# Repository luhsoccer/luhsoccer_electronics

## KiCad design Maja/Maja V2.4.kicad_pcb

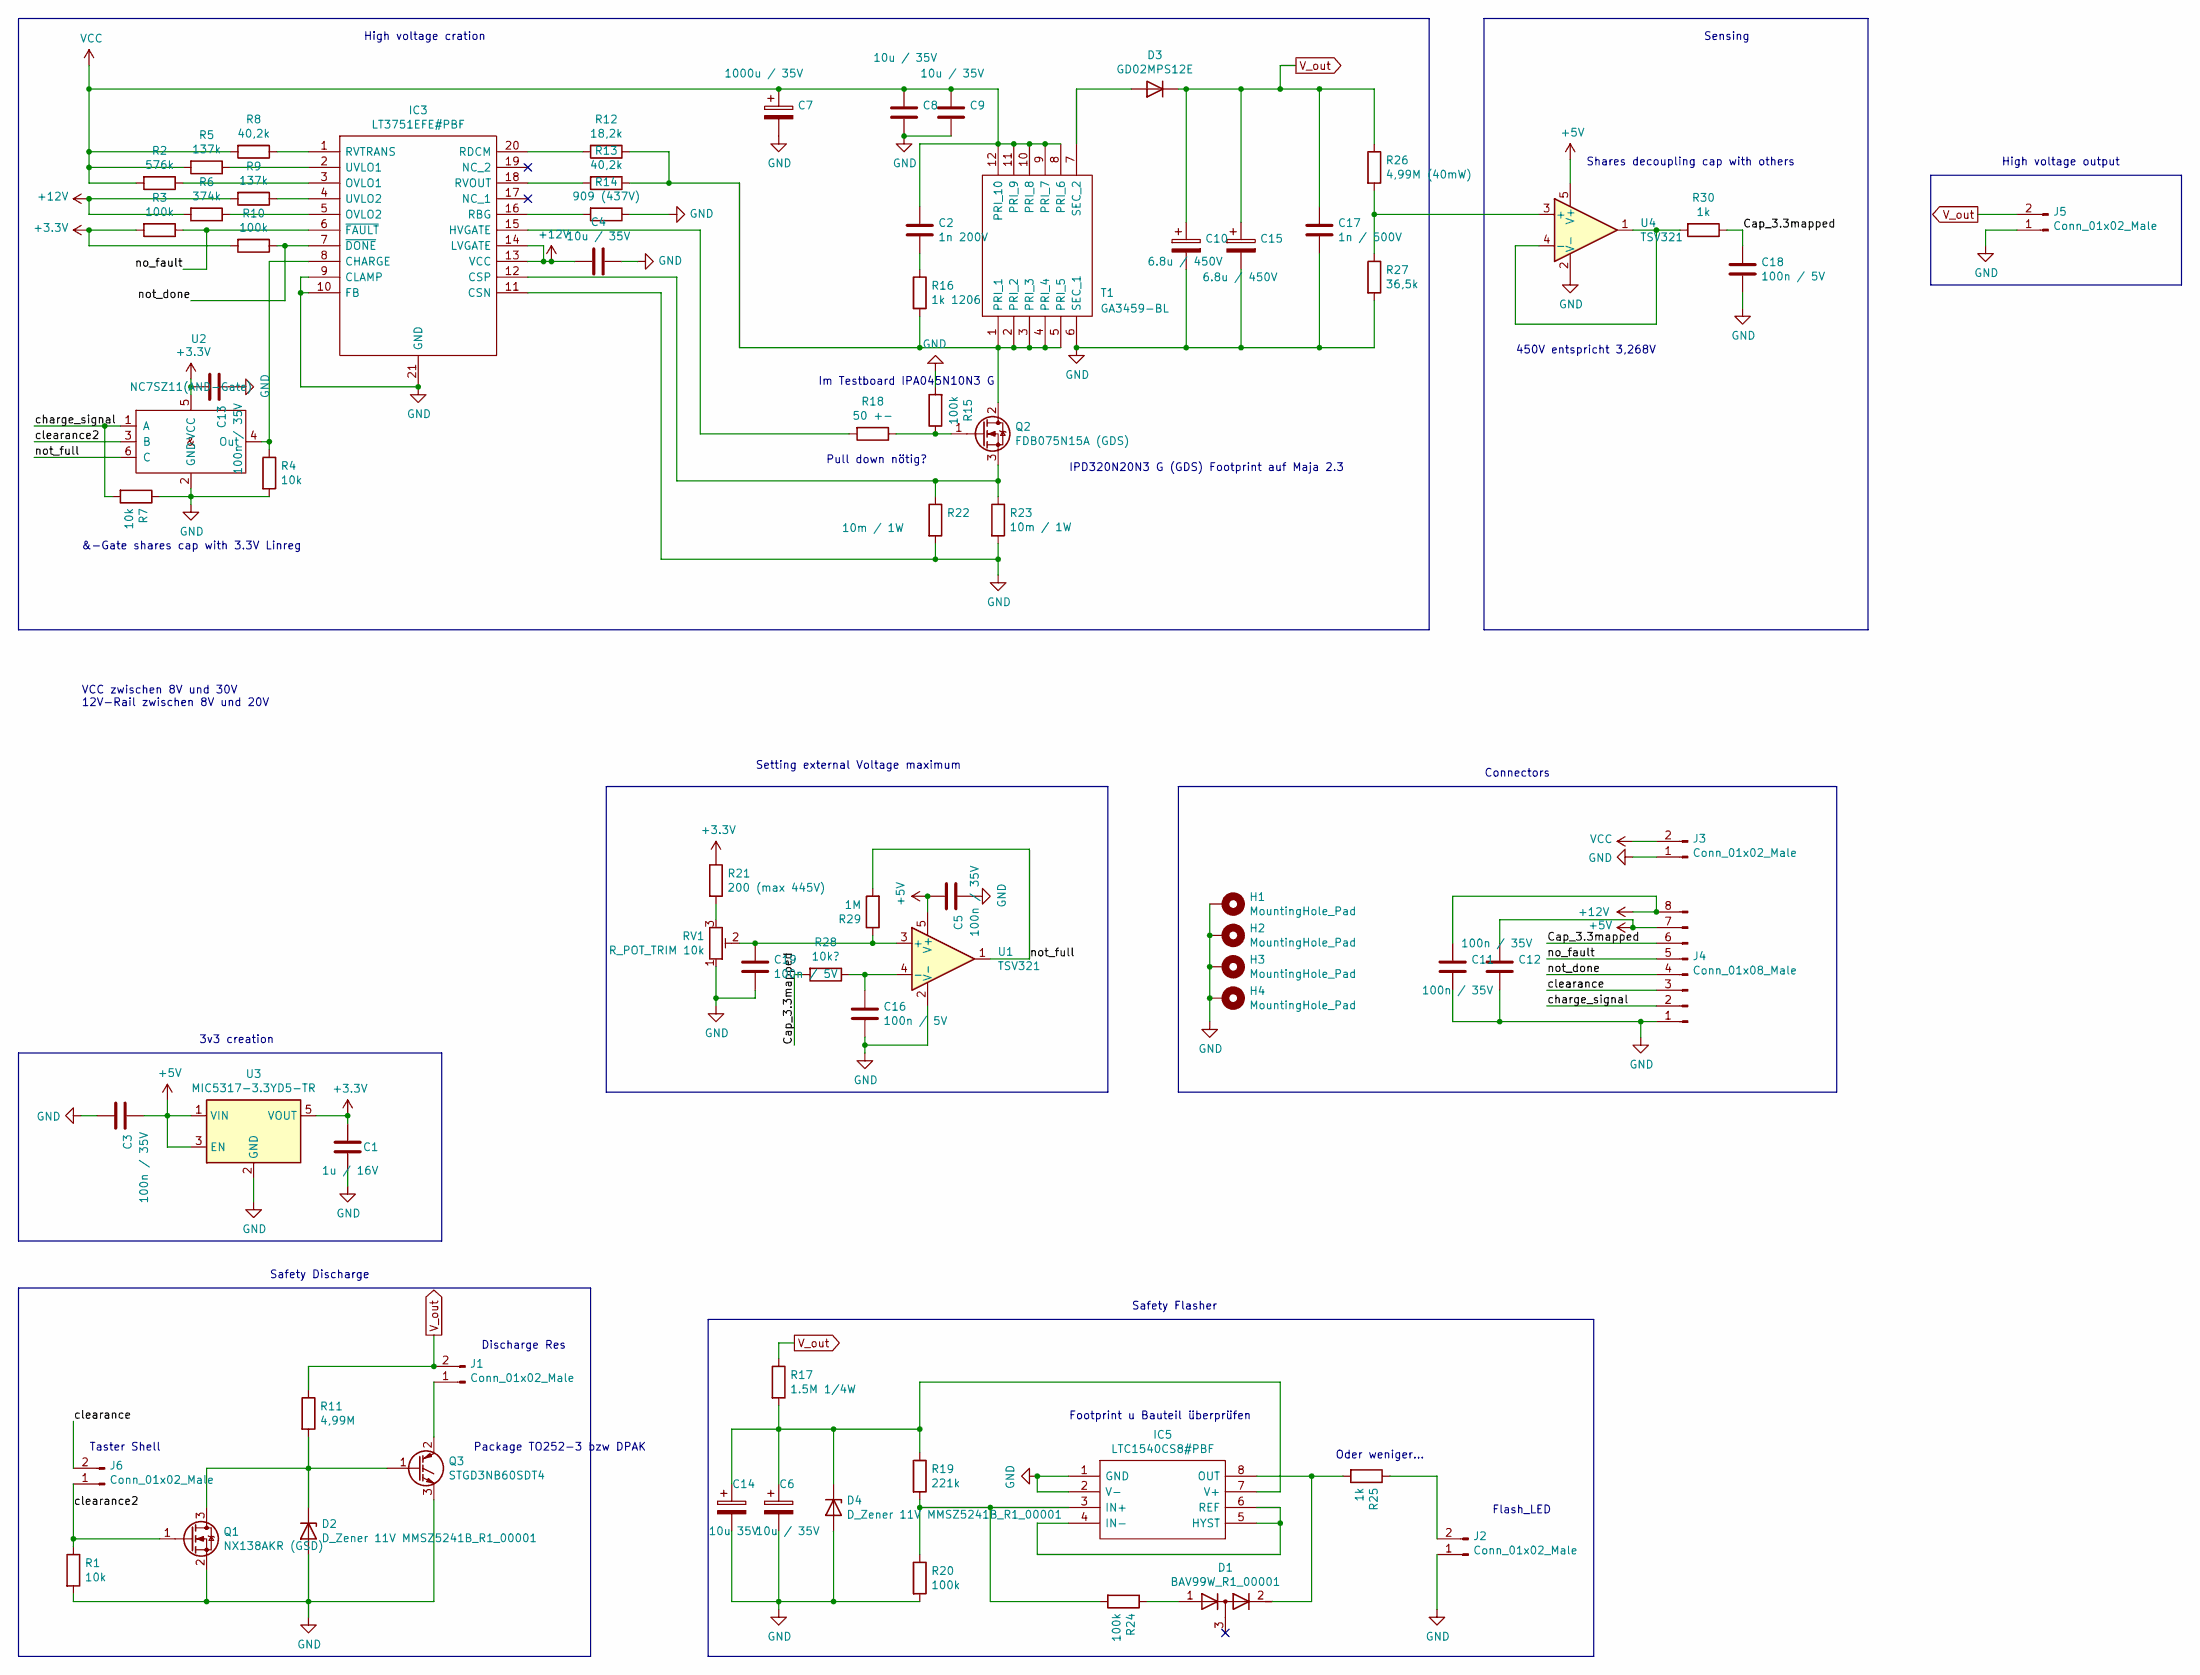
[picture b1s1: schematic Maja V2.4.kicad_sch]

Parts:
C1: 1u / 16V; C_0805_2012Metric_Pad1.15x1.40mm_HandSolder
C2: 1n 200V; C_1206_3216Metric_Pad1.42x1.75mm_HandSolder
C3, C5, C11, C12, C13: 100n / 35V; C_0805_2012Metric_Pad1.15x1.40mm_HandSolder
C4, C6, C8, C9: 10u / 35V; C_0805_2012Metric_Pad1.15x1.40mm_HandSolder
C7: 1000u / 35V; CP_Radial_D16.0mm_P7.50mm
C10, C15: 6.8u / 450V; CP_Radial_D10.0mm_P5.00mm
C14: 10u 35V; C_0805_2012Metric_Pad1.15x1.40mm_HandSolder
C16, C18, C19: 100n / 5V; C_0805_2012Metric_Pad1.15x1.40mm_HandSolder
C17: 1n / 500V; C_1206_3216Metric_Pad1.42x1.75mm_HandSolder
D1: BAV99W_R1_00001; SOT-323_SC-70_Handsoldering
D2, D4: D_Zener 11V MMSZ5241B_R1_00001; D_SOD-123
D3: GD02MPS12E; TO-252-2_TabPin1
H1, H2, H3, H4: MountingHole_Pad; MountingHole_3.2mm_M3_Pad_Via
IC3: LT3751EFE#PBF; SOP65P640X120-21N; Mouser Part Number 584-LT3751EFE#PBF
IC5: LTC1540CS8#PBF; SO-8_3.9x4.9mm_P1.27mm; Mouser Part Number 584-LTC1540IMS8#PBF
J1, J3, J5: Conn_01x02_Male; Molex_Micro-Fit_3.0_43650-0200_1x02_P3.00mm_Horizontal
J2, J6: Conn_01x02_Male; JST_PH_S2B-PH-K_1x02_P2.00mm_Horizontal
J4: Conn_01x08_Male; JST_PH_S8B-PH-K_1x08_P2.00mm_Horizontal
Q1: NX138AKR (GSD); SOT-23_Handsoldering
Q2: FDB075N15A (GDS); TO-263-2
Q3: STGD3NB60SDT4; TO-252-2
R1, R4, R7: 10k; R_0805_2012Metric_Pad1.15x1.40mm_HandSolder
R2: 576k; R_0805_2012Metric_Pad1.15x1.40mm_HandSolder
R3, R10, R15, R20, R24: 100k; R_0805_2012Metric_Pad1.15x1.40mm_HandSolder
R5, R9: 137k; R_0805_2012Metric_Pad1.15x1.40mm_HandSolder
R6: 374k; R_0805_2012Metric_Pad1.15x1.40mm_HandSolder
R8, R13: 40,2k; R_0805_2012Metric_Pad1.15x1.40mm_HandSolder
R11: 4,99M; R_2010_5025Metric_Pad1.52x2.65mm_HandSolder
R12: 18,2k; R_0805_2012Metric_Pad1.15x1.40mm_HandSolder
R14: 909 (437V); R_0805_2012Metric_Pad1.15x1.40mm_HandSolder
R16: 1k 1206; R_1206_3216Metric_Pad1.42x1.75mm_HandSolder
R17: 1.5M 1/4W; R_2010_5025Metric_Pad1.52x2.65mm_HandSolder
R18: 50 +-; R_0805_2012Metric_Pad1.15x1.40mm_HandSolder
R19: 221k; R_0805_2012Metric_Pad1.15x1.40mm_HandSolder
R21: 200 (max 445V); R_0805_2012Metric_Pad1.15x1.40mm_HandSolder
R22, R23: 10m / 1W; R_1206_3216Metric_Pad1.42x1.75mm_HandSolder
R25, R30: 1k; R_0805_2012Metric_Pad1.15x1.40mm_HandSolder
R26: 4,99M (40mW); R_2010_5025Metric_Pad1.52x2.65mm_HandSolder
R27: 36,5k; R_0805_2012Metric_Pad1.15x1.40mm_HandSolder
R28: 10k?; R_0805_2012Metric_Pad1.15x1.40mm_HandSolder
R29: 1M; R_0805_2012Metric_Pad1.15x1.40mm_HandSolder
RV1: R_POT_TRIM 10k; Potentiometer_Bourns_3266Z_Horizontal
T1: GA3459-BL; GA3459BL; Mouser Part Number 994-GA3459-BL
U1, U4: TSV321; TSOT-23-5
U2: NC7SZ11(AND-Gate); SOT-363_SC-70-6_Handsoldering
U3: MIC5317-3.3YD5-TR; SOT-23-5

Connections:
+3V3: C1.2, C13.2, R3.2, R10.2, R21.1, U2.5 (VCC), U3.5 (VOUT)
+5V: C3.1, C5.2, C12.1, J4.7, U1.5 (V+), U3.1 (VIN), U3.3 (EN), U4.5 (V+)
+12V: C4.2, C11.1, IC3.13 (VCC), IC3.14 (LVGATE), J4.8, R6.2, R9.2
/Cap_3.3mapped: C18.1, J4.6, R28.2, R30.1
/charge_signal: J4.2, R7.2, U2.1 (A)
/clearance: J4.3, J6.2
/clearance2: J6.1, Q1.1 (G), R1.1, U2.3 (B)
/no_fault: IC3.6 (~FAULT), J4.5, R3.1
/not_done: IC3.7 (~DONE), J4.4, R10.1
/not_full: R29.2, U1.1, U2.6 (C)
GND: C1.1, C3.2, C4.1, C5.1, C6.2, C7.2, C8.2, C9.2, C10.2, C11.2, C12.2, C13.1, C14.2, C15.2, C16.2, C17.2, C18.2, C19.2, D2.2 (A), D4.2 (A), H1.1, H2.1, H3.1, H4.1, IC3.9 (CLAMP), IC3.10 (FB), IC3.11 (CSN), IC3.21 (GND), IC5.1 (GND), IC5.2 (V-), J2.1, J3.1, J4.1, J5.1, Q1.2 (S), Q3.3 (E), R1.2, R4.2, R7.1, R14.1, R15.2, R20.2, R22.2, R23.2, R27.2, RV1.1, T1.6 (SEC_1), U1.2 (V-), U2.2 (GND), U3.2 (GND), U4.2 (V-)
unnamed: C2.2, R16.1
unnamed: C6.1, C14.1, D4.1 (K), IC5.7 (V+), R17.2, R19.1
unnamed: C16.1, R28.1, U1.4 (-)
unnamed: C19.1, R29.1, RV1.2, U1.3 (+)
unnamed: D1.1 (A), R24.1
unnamed: D1.2 (K), IC5.8 (OUT), R25.2
unnamed: D2.1 (K), Q1.3 (D), Q3.1 (G), R11.2
unnamed: D3.2 (A), T1.7 (SEC_2)
unnamed: IC3.1 (RVTRANS), R8.1
unnamed: IC3.2 (UVLO1), R5.1
unnamed: IC3.3 (OVLO1), R2.1
unnamed: IC3.4 (UVLO2), R9.1
unnamed: IC3.5 (OVLO2), R6.1
unnamed: IC3.8 (CHARGE), R4.1, U2.4 (Out)
unnamed: IC3.12 (CSP), Q2.3 (S), R22.1, R23.1
unnamed: IC3.15 (HVGATE), R18.2
unnamed: IC3.16 (RBG), R14.2
unnamed: IC3.18 (RVOUT), R13.2
unnamed: IC3.20 (RDCM), R12.2
unnamed: IC5.3 (IN+), R19.2, R20.1, R24.2
unnamed: IC5.4 (IN-), IC5.5 (HYST), IC5.6 (REF)
unnamed: J1.1, Q3.2 (C)
unnamed: J2.2, R25.1
unnamed: Q2.1 (G), R15.1, R18.1
unnamed: Q2.2 (D), R12.1, R13.1, R16.2, T1.1 (PRI_1), T1.2 (PRI_2), T1.3 (PRI_3), T1.4 (PRI_4), T1.5 (PRI_5)
unnamed: R21.2, RV1.3
unnamed: R26.2, R27.1, U4.3 (+)
unnamed: R30.2, U4.1, U4.4 (-)
VCC: C2.1, C7.1, C8.1, C9.1, J3.2, R2.2, R5.2, R8.2, T1.8 (PRI_6), T1.9 (PRI_7), T1.10 (PRI_8), T1.11 (PRI_9), T1.12 (PRI_10)
V_out: C10.1, C15.1, C17.1, D3.1 (K), J1.2, J5.2, R11.1, R17.1, R26.1

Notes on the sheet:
Oder weniger...
VCC zwischen 8V und 30V 12V-Rail zwischen 8V und 20V
Flash_LED
Discharge Res
High voltage output
IPD320N20N3 G (GDS) Footprint auf Maja 2.3
Pull down nötig?
Taster Shell
Safety Flasher
Connectors
Setting external Voltage maximum
Im Testboard IPA045N10N3 G
Sensing
&-Gate shares cap with 3.3V Linreg
Shares decoupling cap with others
Footprint u Bauteil überprüfen
High voltage cration
Safety Discharge
450V entspricht 3,268V
Package TO252-3 bzw DPAK
3v3 creation

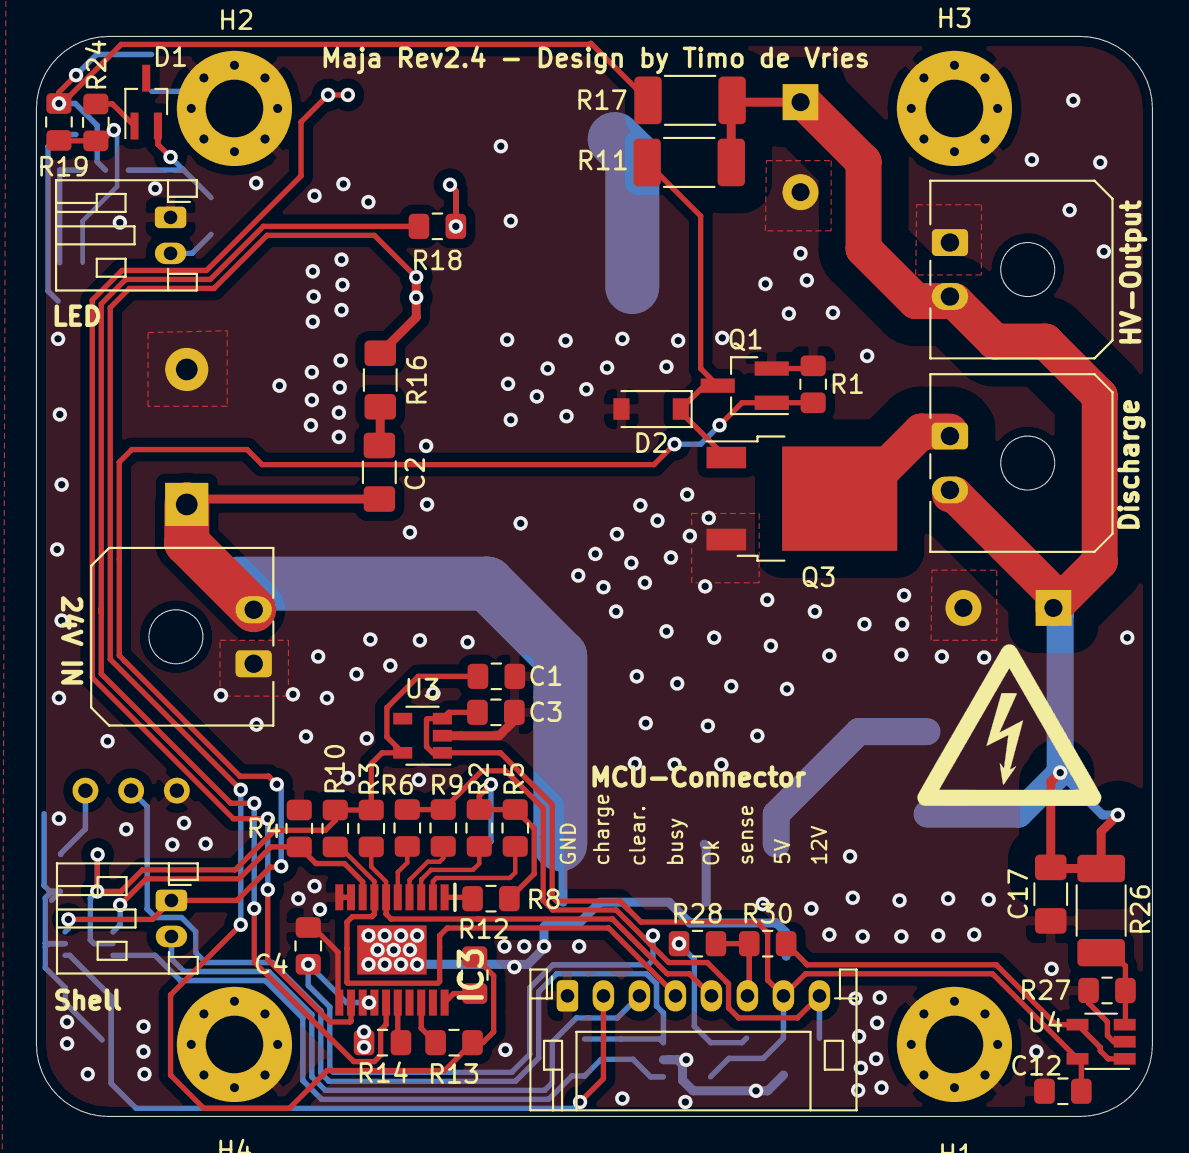
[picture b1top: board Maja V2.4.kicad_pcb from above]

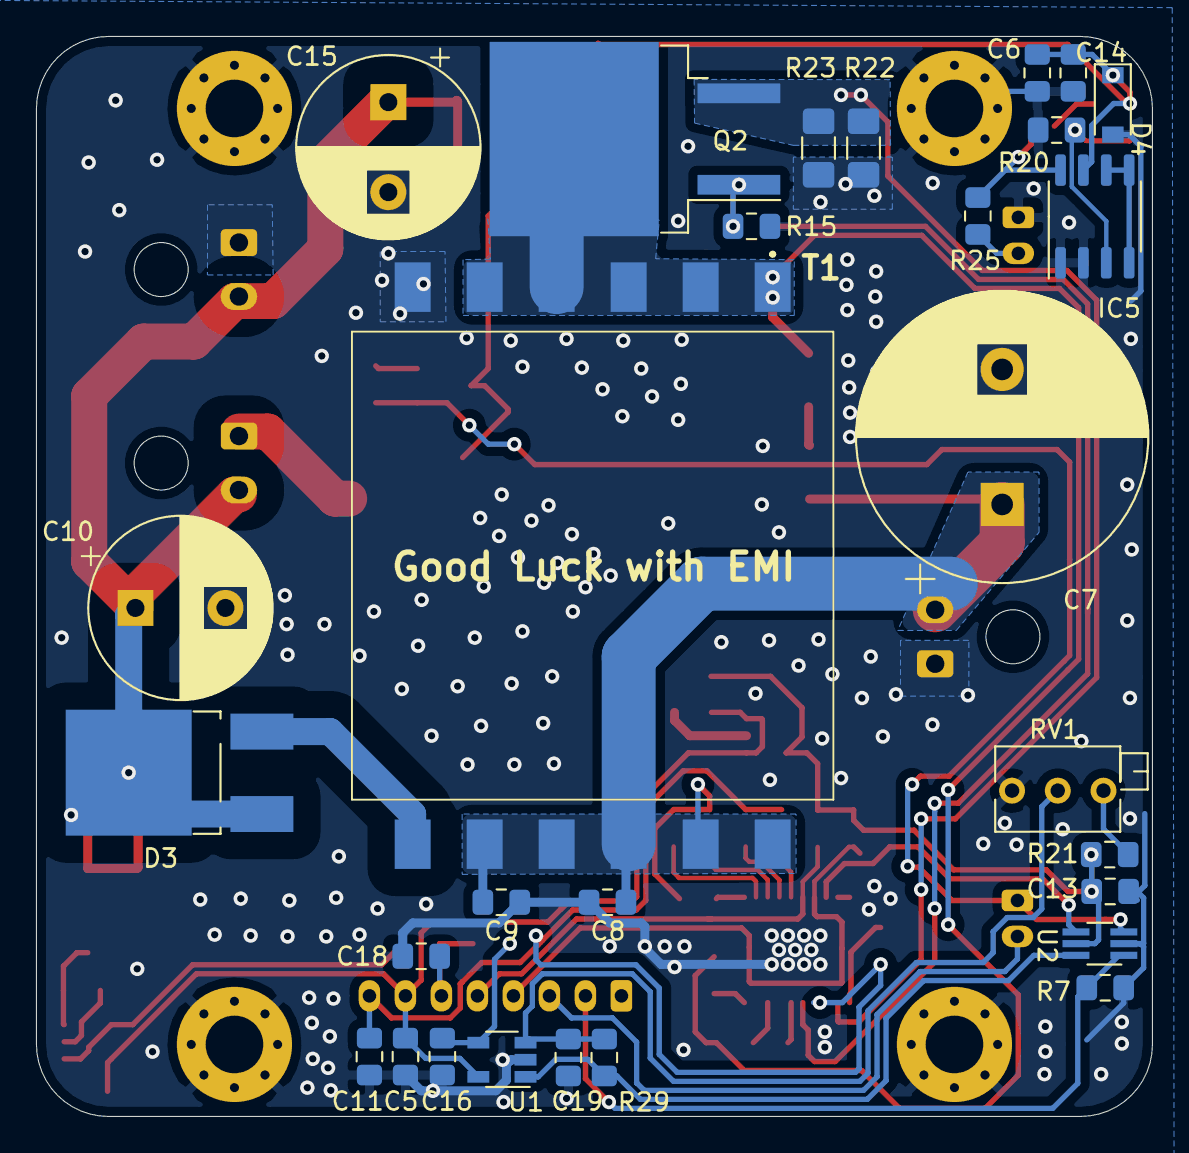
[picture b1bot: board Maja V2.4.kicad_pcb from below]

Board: 2 copper layers, 62.0 x 60.0 mm, 74 parts (29 on the bottom side), 41 nets.

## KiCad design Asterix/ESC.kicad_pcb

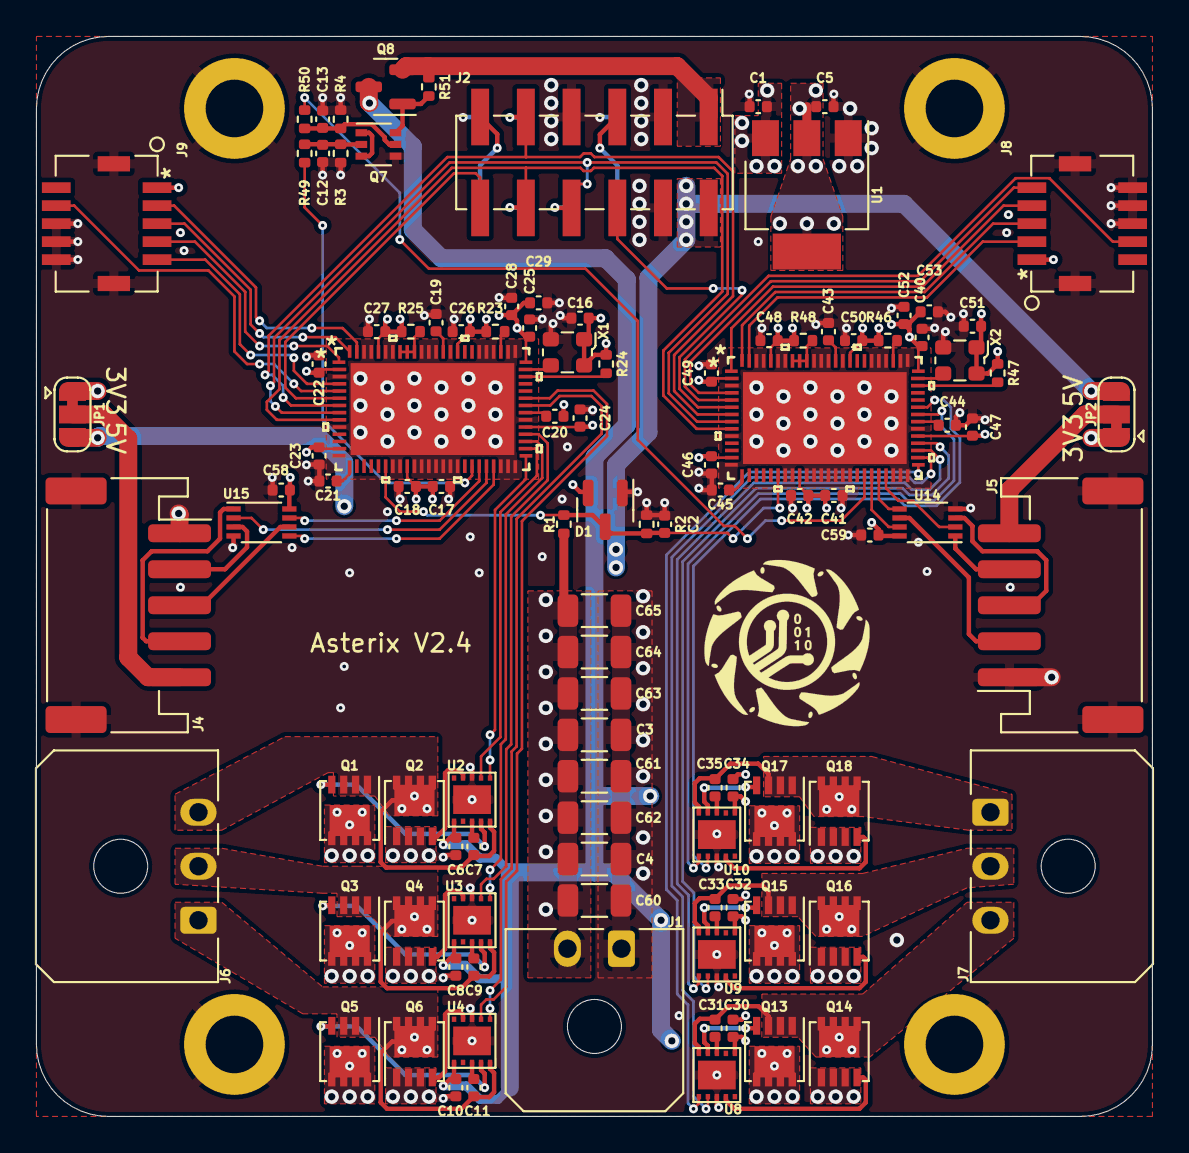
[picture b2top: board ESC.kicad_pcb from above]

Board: 4 copper layers, 62.0 x 60.0 mm, 111 parts (1 on the bottom side), 94 nets.

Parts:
C1, C2, C5, C16, C18, C19, C20, C21, C22, C23, C24, C25, C26, C27, C40, C42, C43, C44, C45, C46, C47, C48, C49, C50, C51, C58, C59: 100nF/50V; C_0402_1005Metric
C3, C4, C60, C61, C62, C63, C64, C65: 10uF/50V; C_1206_3216Metric
C6, C7, C8, C9, C10, C11, C28, C30, C31, C32, C33, C34, C35, C52: 470nF/50V; C_0402_1005Metric
C12, C13: 2u2F/6V3; C_0402_1005Metric
C17, C29, C41, C53: 4u7F/16V; C_0402_1005Metric
D1: BAS40-04; SOT-23
H1, H2, H3, H4: MountingHole_Pad; MountingHole_3.2mm_M3_DIN965_Pad
J1: Power In; Molex_Micro-Fit_3.0_43650-0200_1x02_P3.00mm_Horizontal
J2: TOP_BUS; PinHeader_2x06_P2.54mm_Vertical_SMD
J3: BOTTOM_BUS; PinSocket_2x06_P2.54mm_Vertical_SMD
J4: ESC0_ENC; JST_PH_S5B-PH-SM4-TB_1x05-1MP_P2.00mm_Horizontal
J5: ESC1_ENC; JST_PH_S5B-PH-SM4-TB_1x05-1MP_P2.00mm_Horizontal
J6: ESC0_OUT; Molex_Micro-Fit_3.0_43650-0300_1x03_P3.00mm_Horizontal
J7: ESC1_OUT; Molex_Micro-Fit_3.0_43650-0300_1x03_P3.00mm_Horizontal
J8, J9: Conn_02x05_Odd_Even_MountingPin; DF20F-10DP-1V56
JP1, JP2: SolderJumper_3_Bridged12; SolderJumper-3_P1.3mm_Bridged12_RoundedPad1.0x1.5mm
Q1, Q2, Q3, Q4, Q5, Q6, Q13, Q14, Q15, Q16, Q17, Q18: SiSA72DN; Vishay_PowerPAK_1212-8_Single
Q7: SSM6N44FU,LF; SOT-363_SC-70-6
Q8: PJA3433-AU; SOT-23
R1, R3, R4: 100k; R_0402_1005Metric
R2: 1k5; R_0402_1005Metric
R23, R24, R25, R46, R47, R48: 4k7; R_0402_1005Metric
R49, R50: 1k; R_0402_1005Metric
R51: 22k; R_0402_1005Metric
U1: TLV1117-33; SOT-223-3_TabPin2
U2, U3, U4, U8, U9, U10: MIC4604YMT; TDFN-10_2.5mmx2.5mm
U7, U13: TMC4671
U14, U15: 74LVC3G17; VSSOP-8_2.3x2mm_P0.5mm
X1, X2: ECS-2520MV-250-xx; Oscillator_SMD_ECS_2520MV-xxx-xx-4Pin_2.5x2.0mm

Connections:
+3V3: C5.1, C16.1, C22.2, C23.2, C24.2, C25.2, C26.2, C27.2, C28.1, C29.1, C40.1, C46.2, C47.2, C48.2, C49.2, C50.2, C51.2, C52.1, C53.1, C58.1, C59.1, D1.2, J8.1, J9.1, JP1.1 (A), JP2.1 (A), R23.2, R24.2, R25.2, R46.2, R47.2, R48.2, U1.2 (VO), U7.2 (VCCIO1), U7.13 (VCCIO2), U7.43 (VCCIO3), U7.52 (VCCIO4), U7.61 (VCCIO5), U7.72 (VCCIO6), U13.2 (VCCIO1), U13.13 (VCCIO2), U13.43 (VCCIO3), U13.52 (VCCIO4), U13.61 (VCCIO5), U13.72 (VCCIO6), U14.8 (VCC), U15.8 (VCC), X1.1 (Tri-State), X1.4 (VDD), X2.1 (Tri-State), X2.4 (VDD)
+5V: C1.1, C17.1, C18.2, C41.1, C42.2, J2.2, J3.2, JP1.3 (B), JP2.3 (B), U1.3 (VI), U7.23 (V5), U13.23 (V5)
+12P: J2.1, J3.1, Q8.2 (S), R51.1
+12V: C6.1, C8.1, C10.1, C30.1, C32.1, C34.1, Q8.3 (D), U2.1 (VDD), U3.1 (VDD), U4.1 (VDD), U8.1 (VDD), U9.1 (VDD), U10.1 (VDD)
+24V: C3.1, C4.1, C60.1, C61.1, C62.1, C63.1, C64.1, C65.1, J1.2, Q1.5 (D), Q3.5 (D), Q5.5 (D), Q13.5 (D), Q15.5 (D), Q17.5 (D), R1.1
/ESC0_ControlUnit/CLK_25MHZ: U7.51 (CLK), X1.3 (OUT)
/ESC0_ControlUnit/DBG_MISO: J9.9, U7.4 (GPIO6_/_AENC_VN_MCD_/_DBGSPI_MISO)
/ESC0_ControlUnit/DBG_MOSI: J9.7, U7.1 (GPIO5_/_AENC_UX_MCD_/_DBGSPI_MOSI)
/ESC0_ControlUnit/DBG_NCS: J9.3, U7.75 (GPIO3_/_AGPI_A_MCD_/_DBGSPI_nSCS)
/ESC0_ControlUnit/DBG_SCK: J9.5, U7.76 (GPIO4_/_AGPI_B_MCD_/_DBGSPI_SCK)
/ESC0_ControlUnit/DBG_TRG: J9.4, U7.5 (GPIO7_/_AENC_WY_MCD_/_DBGSPI_TRG)
/ESC0_ControlUnit/ENC_A: U7.35 (ENC_A), U15.5
/ESC0_ControlUnit/ENC_B: U7.34 (ENC_B), U15.2
/ESC0_ControlUnit/ENC_N: U7.33 (ENC_N), U15.7
/ESC0_ControlUnit/ENI: R23.1, U7.55 (ENI)
/ESC0_ControlUnit/NRST: R24.1, U7.50 (nRST)
/ESC0_ControlUnit/PWM_U_H: U2.6 (HI), U7.39 (PWM_UX1_H)
/ESC0_ControlUnit/PWM_U_L: U2.7 (LI), U7.40 (PWM_UX1_L)
/ESC0_ControlUnit/PWM_V_H: U3.6 (HI), U7.41 (PWM_VX2_H)
/ESC0_ControlUnit/PWM_V_L: U3.7 (LI), U7.42 (PWM_VX2_L)
/ESC0_ControlUnit/PWM_W_H: U4.6 (HI), U7.46 (PWM_WY1_H)
/ESC0_ControlUnit/PWM_W_L: U4.7 (LI), U7.47 (PWM_WY1_L)
/ESC0_ControlUnit/REF_LHR: R25.1, U7.67 (REF_L), U7.68 (REF_H), U7.69 (REF_R)
/ESC0_ControlUnit/V_CORE_1: C21.2, U7.15 (VCCCORE1)
/ESC0_ControlUnit/V_CORE_2: C20.2, U7.45 (VCCCORE2)
/ESC0_ControlUnit/V_CORE_3: C19.2, U7.63 (VCCCORE3)
/ESC0_ENC_A_IN: J4.2, U15.3
/ESC0_ENC_B_IN: J4.3, U15.6
/ESC0_ENC_N_IN: J4.4, U15.1
/ESC0_EN_OUT: R49.1, U7.32 (ENO)
/ESC0_PowerStageU/CHARGE_P: C7.1, U2.3 (HB)
/ESC0_PowerStageU/GATE_H: Q1.4 (G), U2.4 (HO)
/ESC0_PowerStageU/GATE_L: Q2.4 (G), U2.9 (LO)
/ESC0_PowerStageV/CHARGE_P: C9.1, U3.3 (HB)
/ESC0_PowerStageV/GATE_H: Q3.4 (G), U3.4 (HO)
/ESC0_PowerStageV/GATE_L: Q4.4 (G), U3.9 (LO)
/ESC0_PowerStageW/CHARGE_P: C11.1, U4.3 (HB)
/ESC0_PowerStageW/GATE_H: Q5.4 (G), U4.4 (HO)
/ESC0_PowerStageW/GATE_L: Q6.4 (G), U4.9 (LO)
/ESC0_U_SHUNT_P: C11.2, J6.1, Q5.1 (S), Q5.2 (S), Q5.3 (S), Q6.5 (D), U4.5 (HS)
/ESC0_V_SHUNT_P: C9.2, J6.2, Q3.1 (S), Q3.2 (S), Q3.3 (S), Q4.5 (D), U3.5 (HS)
/ESC0_W_OUT: C7.2, J6.3, Q1.1 (S), Q1.2 (S), Q1.3 (S), Q2.5 (D), U2.5 (HS)
/ESC1_ControlUnit/CLK_25MHZ: U13.51 (CLK), X2.3 (OUT)
/ESC1_ControlUnit/DBG_MISO: J8.9, U13.4 (GPIO6_/_AENC_VN_MCD_/_DBGSPI_MISO)
/ESC1_ControlUnit/DBG_MOSI: J8.7, U13.1 (GPIO5_/_AENC_UX_MCD_/_DBGSPI_MOSI)
/ESC1_ControlUnit/DBG_NCS: J8.3, U13.75 (GPIO3_/_AGPI_A_MCD_/_DBGSPI_nSCS)
/ESC1_ControlUnit/DBG_SCK: J8.5, U13.76 (GPIO4_/_AGPI_B_MCD_/_DBGSPI_SCK)
/ESC1_ControlUnit/DBG_TRG: J8.4, U13.5 (GPIO7_/_AENC_WY_MCD_/_DBGSPI_TRG)
/ESC1_ControlUnit/ENC_A: U13.35 (ENC_A), U14.2
/ESC1_ControlUnit/ENC_B: U13.34 (ENC_B), U14.5
/ESC1_ControlUnit/ENC_N: U13.33 (ENC_N), U14.7
/ESC1_ControlUnit/ENI: R46.1, U13.55 (ENI)
/ESC1_ControlUnit/NRST: R47.1, U13.50 (nRST)
/ESC1_ControlUnit/PWM_U_H: U8.6 (HI), U13.39 (PWM_UX1_H)
/ESC1_ControlUnit/PWM_U_L: U8.7 (LI), U13.40 (PWM_UX1_L)
/ESC1_ControlUnit/PWM_V_H: U9.6 (HI), U13.41 (PWM_VX2_H)
/ESC1_ControlUnit/PWM_V_L: U9.7 (LI), U13.42 (PWM_VX2_L)
/ESC1_ControlUnit/PWM_W_H: U10.6 (HI), U13.46 (PWM_WY1_H)
/ESC1_ControlUnit/PWM_W_L: U10.7 (LI), U13.47 (PWM_WY1_L)
/ESC1_ControlUnit/REF_LHR: R48.1, U13.67 (REF_L), U13.68 (REF_H), U13.69 (REF_R)
/ESC1_ControlUnit/V_CORE_1: C45.2, U13.15 (VCCCORE1)
/ESC1_ControlUnit/V_CORE_2: C44.2, U13.45 (VCCCORE2)
/ESC1_ControlUnit/V_CORE_3: C43.2, U13.63 (VCCCORE3)
/ESC1_ENC_A_IN: J5.2, U14.6
/ESC1_ENC_B_IN: J5.3, U14.3
/ESC1_ENC_N_IN: J5.4, U14.1
/ESC1_EN_OUT: R50.1, U13.32 (ENO)
/ESC1_PowerStageU/CHARGE_P: C31.1, U8.3 (HB)
/ESC1_PowerStageU/GATE_H: Q13.4 (G), U8.4 (HO)
/ESC1_PowerStageU/GATE_L: Q14.4 (G), U8.9 (LO)
/ESC1_PowerStageV/CHARGE_P: C33.1, U9.3 (HB)
/ESC1_PowerStageV/GATE_H: Q15.4 (G), U9.4 (HO)
/ESC1_PowerStageV/GATE_L: Q16.4 (G), U9.9 (LO)
/ESC1_PowerStageW/CHARGE_P: C35.1, U10.3 (HB)
/ESC1_PowerStageW/GATE_H: Q17.4 (G), U10.4 (HO)
/ESC1_PowerStageW/GATE_L: Q18.4 (G), U10.9 (LO)
/ESC1_U_SHUNT_P: C31.2, J7.3, Q13.1 (S), Q13.2 (S), Q13.3 (S), Q14.5 (D), U8.5 (HS)
/ESC1_V_SHUNT_P: C33.2, J7.2, Q15.1 (S), Q15.2 (S), Q15.3 (S), Q16.5 (D), U9.5 (HS)
/ESC1_W_OUT: C35.2, J7.1, Q17.1 (S), Q17.2 (S), Q17.3 (S), Q18.5 (D), U10.5 (HS)
/MISO: J2.10, J3.10, U7.9 (SPI_MISO), U13.9 (SPI_MISO)
/MOSI: J2.8, J3.8, U7.8 (SPI_MOSI), U13.8 (SPI_MOSI)
/NCS0: J2.12, U7.6 (SPI_nSCS)
/NCS1: J2.6, U13.6 (SPI_nSCS)
/NCS2: J2.11, J3.12
/NCS3: J2.5, J3.6
/SCK: J2.9, J3.9, U7.7 (SPI_SCK), U13.7 (SPI_SCK)
/VMOT_SENSE: C2.1, D1.3, R1.2, R2.1, U7.20 (ADC_VM), U13.20 (ADC_VM)
GND: C1.2, C2.2, C3.2, C4.2, C5.2, C6.2, C8.2, C10.2, C12.2, C13.2, C16.2, C17.2, C18.1, C19.1, C20.1, C21.1, C22.1, C23.1, C24.1, C25.1, C26.1, C27.1, C28.2, C29.2, C30.2, C32.2, C34.2, C40.2, C41.2, C42.1, C43.1, C44.1, C45.1, C46.1, C47.1, C48.1, C49.1, C50.1, C51.1, C52.2, C53.2, C58.2, C59.2, C60.2, C61.2, C62.2, C63.2, C64.2, C65.2, D1.1, H1.1, H2.1, H3.1, H4.1, J1.1, J2.3, J2.4, J2.7, J3.3, J3.4, J3.5, J3.7, J3.11, J4.1, J4.MP (MountPin), J5.1, J5.MP (MountPin), J8.6, J8.8, J8.10, J8.MP (MountPin), J9.6, J9.8, J9.10, J9.MP (MountPin), Q2.1 (S), Q2.2 (S), Q2.3 (S), Q4.1 (S), Q4.2 (S), Q4.3 (S), Q6.1 (S), Q6.2 (S), Q6.3 (S), Q7.4 (S), Q14.1 (S), Q14.2 (S), Q14.3 (S), Q16.1 (S), Q16.2 (S), Q16.3 (S), Q18.1 (S), Q18.2 (S), Q18.3 (S), R2.2, R3.2, R4.2, U1.1 (GND), U2.8 (VSS), U2.11 (VSS), U3.8 (VSS), U3.11 (VSS), U4.8 (VSS), U4.11 (VSS), U7.3 (GNDIO1), U7.10 (UART_RXD), U7.14 (GNDIO2), U7.21 (AGPI_A), U7.22 (AGPI_B), U7.24 (GNDA), U7.25 (AENC_UX_POS), U7.26 (AENC_UX_NEG), U7.27 (AENC_VN_POS), U7.28 (AENC_VN_NEG), U7.29 (AENC_WY_POS), U7.30 (AENC_WY_NEG), U7.36 (HALL_WY), U7.37 (HALL_V), U7.38 (HALL_UX), U7.44 (GNDIO3), U7.53 (GNDIO4), U7.54 (TEST), U7.56 (DIR), U7.57 (STP), U7.58 (PWM_I), U7.62 (GNDIO5), U7.64 (ENC2_A), U7.65 (ENC2_B), U7.66 (ENC2_N), U7.70 (GPIO0_/_ADC_I0_MCD), U7.71 (GPIO1_/_ADC_I1_MCD), U7.73 (GNDIO6), U7.74 (GPIO2_/_ADC_VM_MCD), U7.77 (GNDPAD), U8.8 (VSS), U8.11 (VSS), U9.8 (VSS), U9.11 (VSS), U10.8 (VSS), U10.11 (VSS), U13.3 (GNDIO1), U13.10 (UART_RXD), U13.14 (GNDIO2), U13.21 (AGPI_A), U13.22 (AGPI_B), U13.24 (GNDA), U13.25 (AENC_UX_POS), U13.26 (AENC_UX_NEG), U13.27 (AENC_VN_POS), U13.28 (AENC_VN_NEG), U13.29 (AENC_WY_POS), U13.30 (AENC_WY_NEG), U13.36 (HALL_WY), U13.37 (HALL_V), U13.38 (HALL_UX), U13.44 (GNDIO3), U13.53 (GNDIO4), U13.54 (TEST), U13.56 (DIR), U13.57 (STP), U13.58 (PWM_I), U13.62 (GNDIO5), U13.64 (ENC2_A), U13.65 (ENC2_B), U13.66 (ENC2_N), U13.70 (GPIO0_/_ADC_I0_MCD), U13.71 (GPIO1_/_ADC_I1_MCD), U13.73 (GNDIO6), U13.74 (GPIO2_/_ADC_VM_MCD), U13.77 (GNDPAD), U14.4 (GND), U15.4 (GND), X1.2 (GND), X2.2 (GND)
unnamed: C12.1, Q7.2 (G), R3.1, R49.2
unnamed: C13.1, Q7.5 (G), R4.1, R50.2
unnamed: J4.5, JP1.2 (C)
unnamed: J5.5, JP2.2 (C)
unnamed: Q7.1 (S), Q7.3 (D)
unnamed: Q7.6 (D), Q8.1 (G), R51.2

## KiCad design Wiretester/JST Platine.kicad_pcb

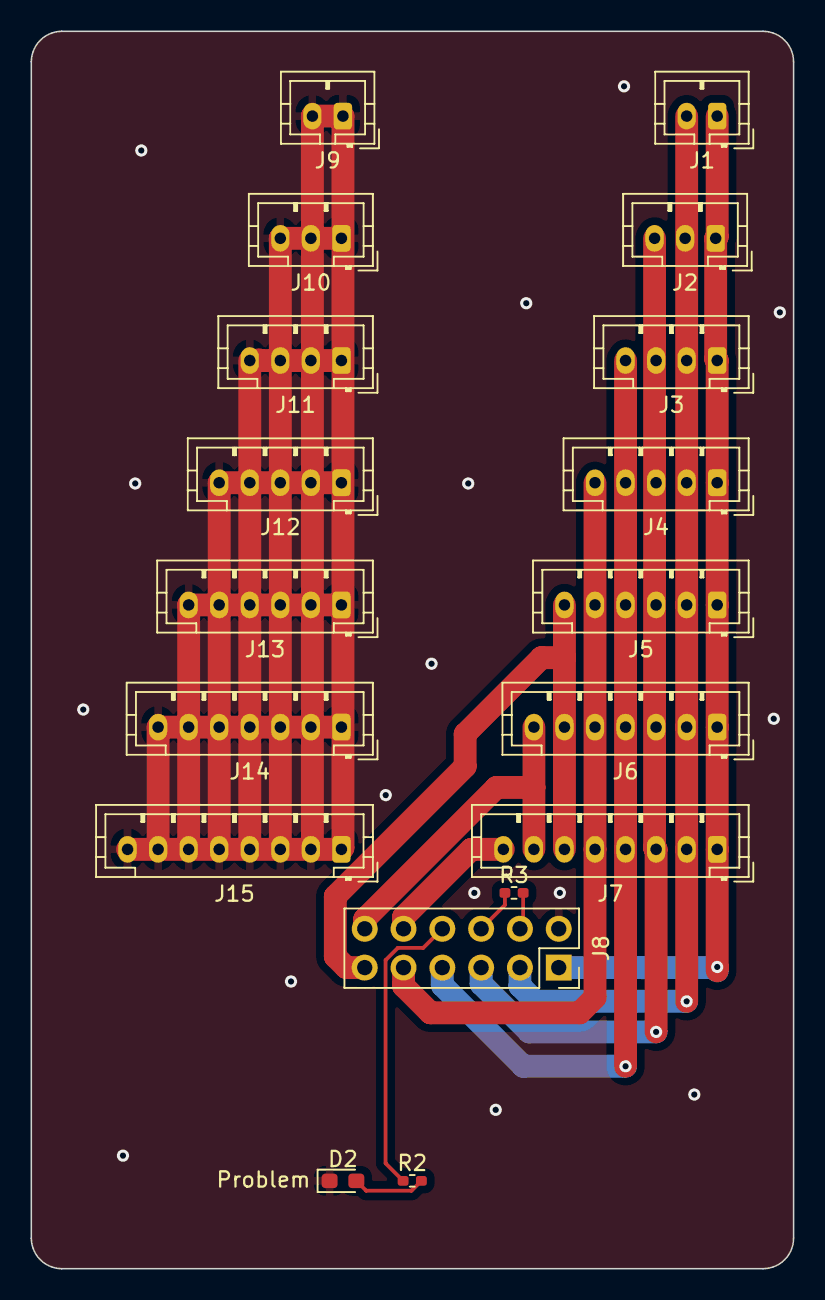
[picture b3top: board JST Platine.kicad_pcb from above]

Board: 2 copper layers, 49.9 x 81.0 mm, 18 parts (0 on the bottom side), 13 nets.

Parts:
D2: LED; LED_0603_1608Metric_Pad1.05x0.95mm_HandSolder
J1, J9: Conn_01x02; JST_PH_B2B-PH-K_1x02_P2.00mm_Vertical
J2, J10: Conn_01x03; JST_PH_B3B-PH-K_1x03_P2.00mm_Vertical
J3, J11: Conn_01x04; JST_PH_B4B-PH-K_1x04_P2.00mm_Vertical
J4, J12: Conn_01x05; JST_PH_B5B-PH-K_1x05_P2.00mm_Vertical
J5, J13: Conn_01x06; JST_PH_B6B-PH-K_1x06_P2.00mm_Vertical
J6, J14: Conn_01x07; JST_PH_B7B-PH-K_1x07_P2.00mm_Vertical
J7, J15: Conn_01x08; JST_PH_B8B-PH-K_1x08_P2.00mm_Vertical
J8: Conn_02x06_Odd_Even; PinSocket_2x06_P2.54mm_Vertical
R2: 470; R_0402_1005Metric_Pad0.72x0.64mm_HandSolder
R3: R; R_0402_1005Metric_Pad0.72x0.64mm_HandSolder

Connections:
/ADC: J8.6, R3.1
/GPIO: J8.4, R3.2
/GPIO9: J8.8, R2.1
GND: D2.1 (K), J8.2, J9.1, J9.2, J10.1, J10.2, J10.3, J11.1, J11.2, J11.3, J11.4, J12.1, J12.2, J12.3, J12.4, J12.5, J13.1, J13.2, J13.3, J13.4, J13.5, J13.6, J14.1, J14.2, J14.3, J14.4, J14.5, J14.6, J14.7, J15.1, J15.2, J15.3, J15.4, J15.5, J15.6, J15.7, J15.8
unnamed: D2.2 (A), R2.2
unnamed: J1.1, J2.1, J3.1, J4.1, J5.1, J6.1, J7.1, J8.1
unnamed: J1.2, J2.2, J3.2, J4.2, J5.2, J6.2, J7.2, J8.3
unnamed: J2.3, J3.3, J4.3, J5.3, J6.3, J7.3, J8.5
unnamed: J3.4, J4.4, J5.4, J6.4, J7.4, J8.7
unnamed: J4.5, J5.5, J6.5, J7.5, J8.9
unnamed: J5.6, J6.6, J7.6, J8.11
unnamed: J6.7, J7.7, J8.12
unnamed: J7.8, J8.10

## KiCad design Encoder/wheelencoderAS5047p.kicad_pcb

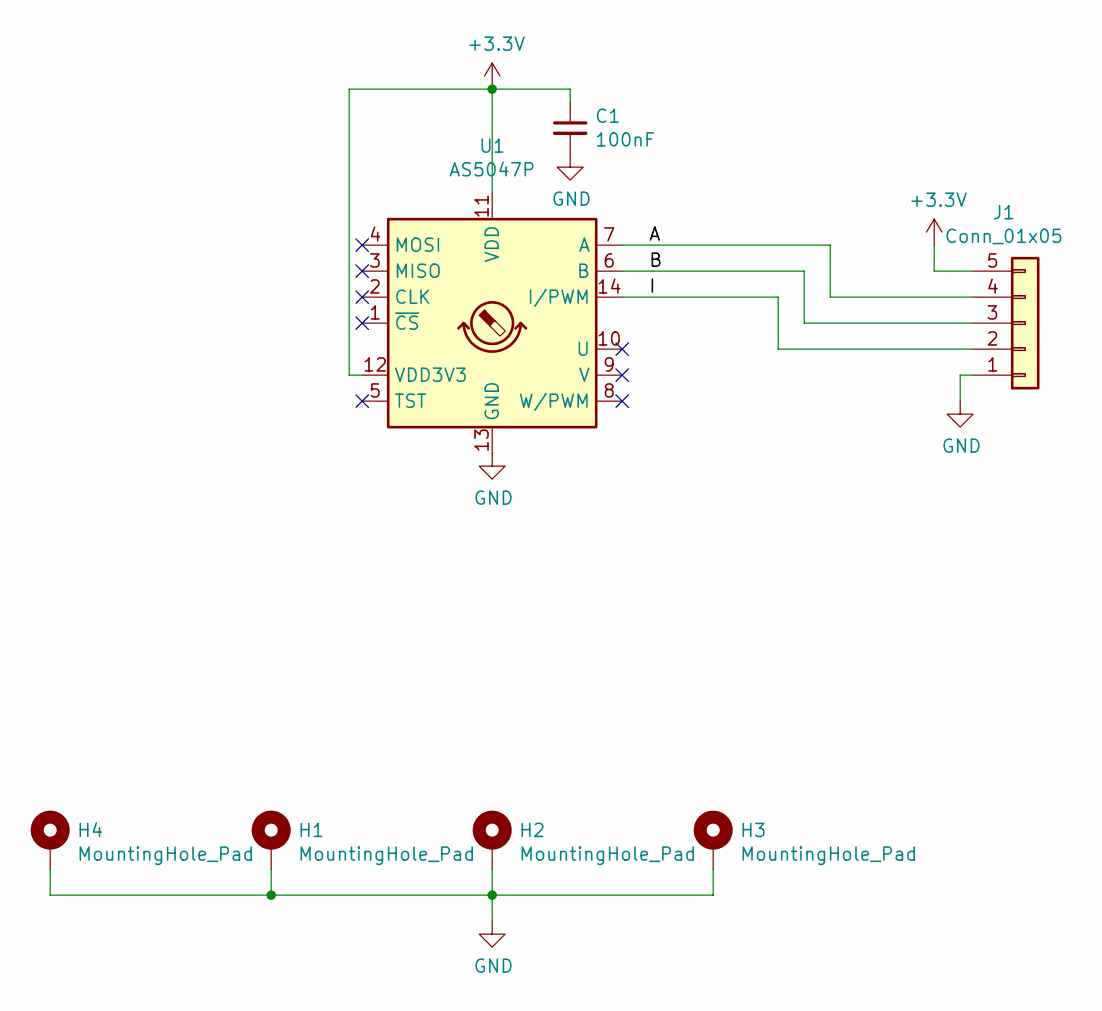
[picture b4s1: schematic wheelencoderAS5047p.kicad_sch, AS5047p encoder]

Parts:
C1: 100nF; C_0805_2012Metric_Pad1.18x1.45mm_HandSolder
H1, H2, H3, H4: MountingHole_Pad; MountingHole_3.2mm_M3_DIN965_Pad
J1: Conn_01x05; JST_PH_S5B-PH-K_1x05_P2.00mm_Horizontal
U1: AS5047P; TSSOP-14_4.4x5mm_P0.65mm

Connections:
+3V3: C1.1, J1.5, U1.11 (VDD), U1.12 (VDD3V3)
/A: J1.4, U1.7 (A)
/B: J1.3, U1.6 (B)
/I: J1.2, U1.14 (I/PWM)
GND: C1.2, H1.1, H2.1, H3.1, H4.1, J1.1, U1.13 (GND)

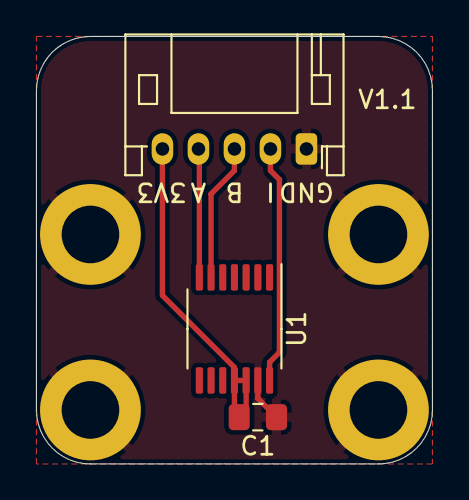
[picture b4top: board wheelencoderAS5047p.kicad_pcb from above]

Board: 2 copper layers, 22.0 x 23.8 mm, 7 parts (0 on the bottom side), 5 nets.

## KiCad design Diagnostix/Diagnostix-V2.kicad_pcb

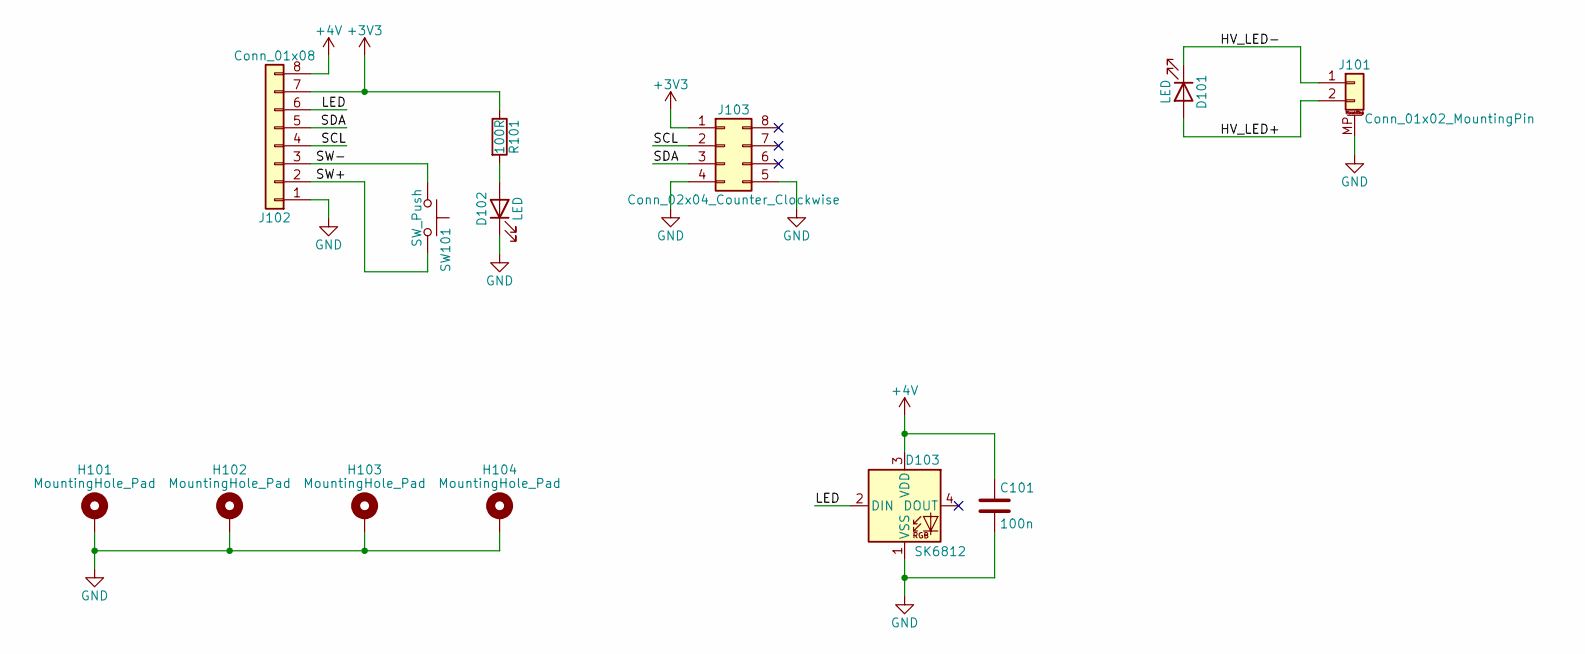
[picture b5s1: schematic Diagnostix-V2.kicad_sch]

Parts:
C101: 100n; C_0402_1005Metric
D101, D102: LED; LED_0603_1608Metric
D103: SK6812; LED_SK6812_PLCC4_5.0x5.0mm_P3.2mm
H101, H102, H103, H104: MountingHole_Pad; MountingHole_3.2mm_M3_DIN965_Pad
J101: Conn_01x02_MountingPin; JST_PH_S2B-PH-SM4-TB_1x02-1MP_P2.00mm_Horizontal
J102: Conn_01x08; JST_PH_S8B-PH-K_1x08_P2.00mm_Horizontal
J103: Conn_02x04_Counter_Clockwise; IDC-Header_2x04_P2.54mm_Vertical
R101: 100R; R_0402_1005Metric
SW101: SW_Push; SW_SPST_TL3305A

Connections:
+3V3: J102.7, J103.1, R101.1
+4V: C101.1, D103.3 (VDD), J102.8
/HV_LED+: D101.2 (A), J101.2
/HV_LED-: D101.1 (K), J101.1
/LED: D103.2 (DIN), J102.6
/SCL: J102.4, J103.2
/SDA: J102.5, J103.3
/SW+: J102.2, SW101.2
/SW-: J102.3, SW101.1
GND: C101.2, D102.1 (K), D103.1 (VSS), H101.1, H102.1, H103.1, H104.1, J101.MP (MountPin), J102.1, J103.4, J103.5
unnamed: D102.2 (A), R101.2

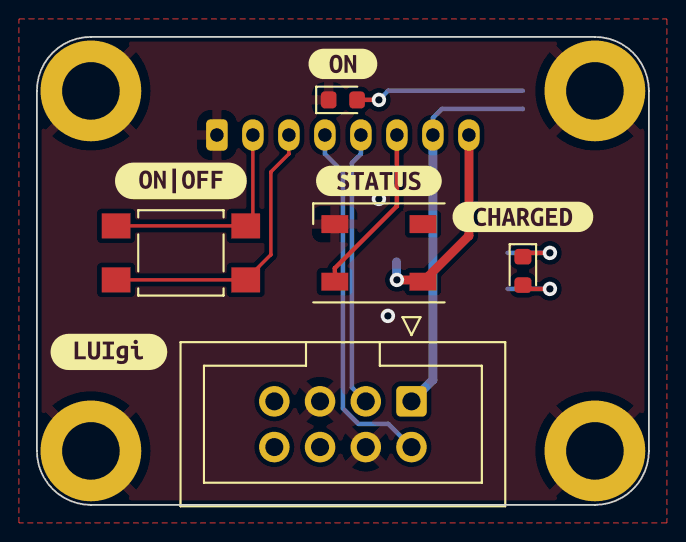
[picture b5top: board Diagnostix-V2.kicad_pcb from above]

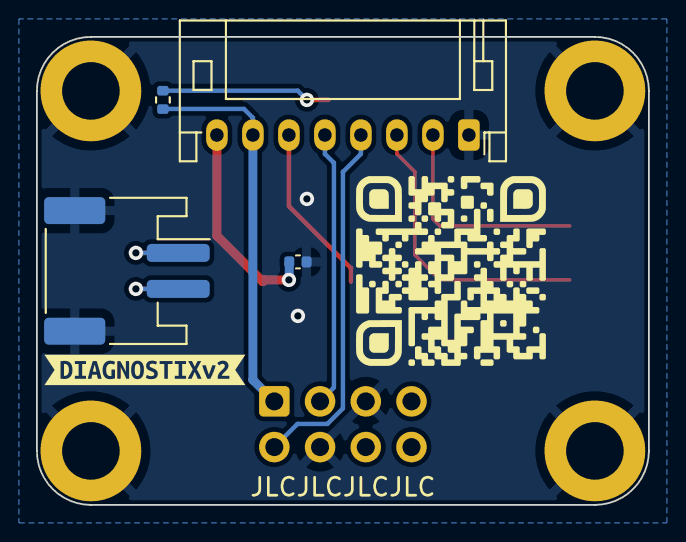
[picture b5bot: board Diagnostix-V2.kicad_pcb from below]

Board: 2 copper layers, 34.0 x 26.0 mm, 19 parts (5 on the bottom side), 11 nets.

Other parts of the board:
kibuzzard-634D60B1: G***; kibuzzard-634D60B1
kibuzzard-634D60CF: G***; kibuzzard-634D60CF
kibuzzard-634D607E: G***; kibuzzard-634D607E
kibuzzard-634D6074: G***; kibuzzard-634D6074
kibuzzard-634D6139: G***; kibuzzard-634D6139
kibuzzard-634D6434: G***; kibuzzard-634D6434

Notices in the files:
parts and their libraries:
Copyright 2016 Accelerated Designs. All rights reserved.
Copyright 2021 Accelerated Designs. All rights reserved.
